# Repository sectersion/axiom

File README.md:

# axiom

modules are 10x15mm note

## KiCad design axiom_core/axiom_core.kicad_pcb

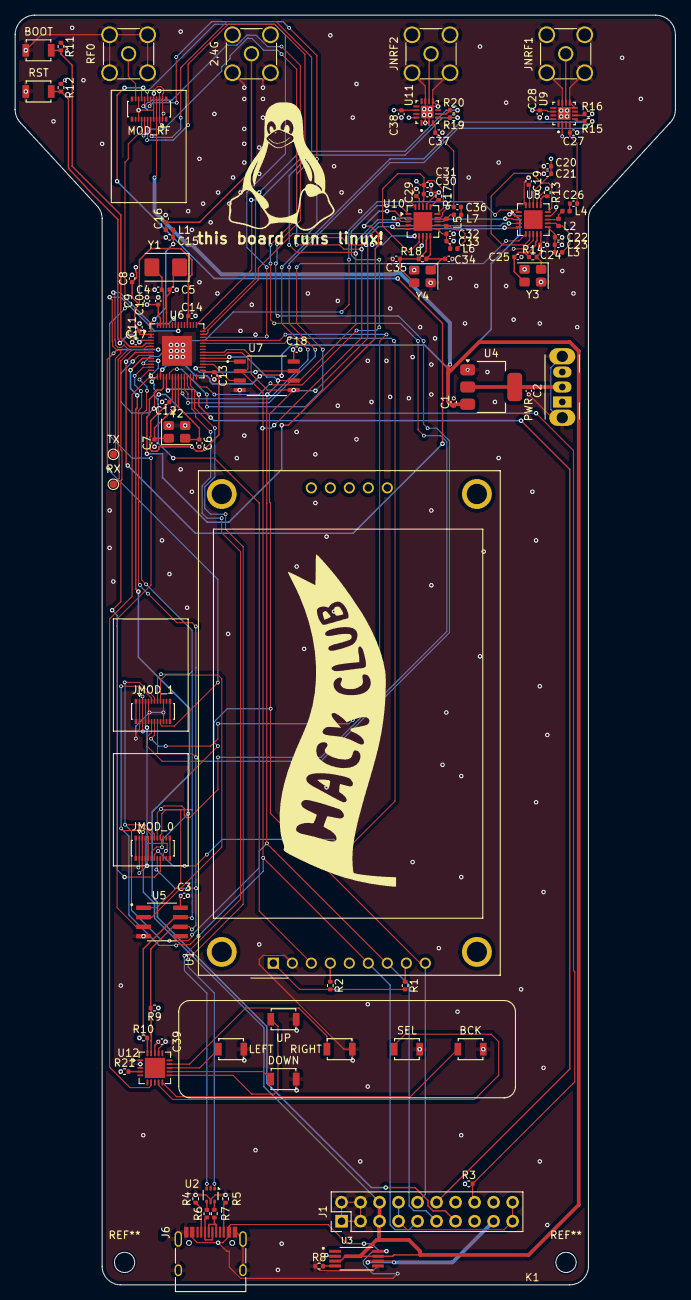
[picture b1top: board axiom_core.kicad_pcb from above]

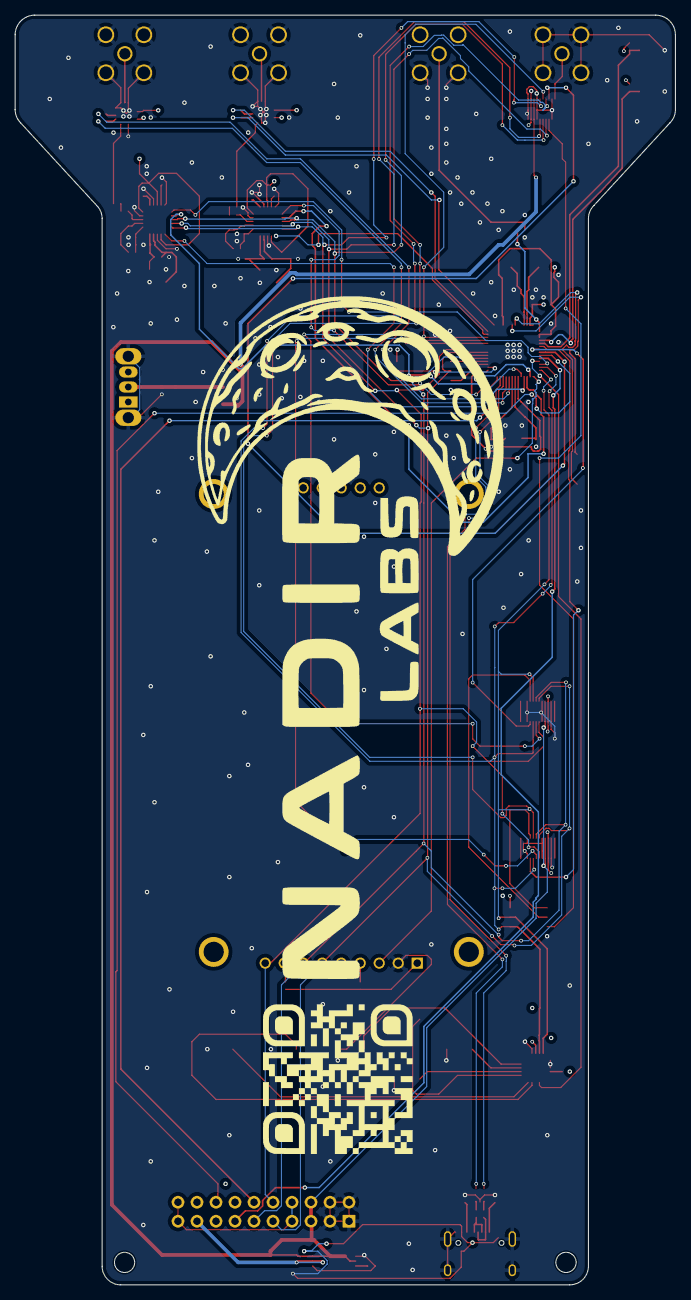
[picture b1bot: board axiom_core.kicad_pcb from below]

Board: 4 copper layers, 88.2 x 169.7 mm, 108 parts (2 on the bottom side), 91 nets.

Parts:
2.4G: ESP32_2.4G; SMA_Amphenol_901-144_Vertical
BCK: BCK; SW_SPST_B3U-1000P
BOOT: BOOT; SW_SPST_B3U-1000P
C1, C10: 10uF; C_0402_1005Metric
C2: 22uF; C_0402_1005Metric
C3, C9, C11, C12, C13, C14, C17, C18, C28, C38, C39: 100nF; C_0402_1005Metric
C4, C5: 18pF; C_0402_1005Metric
C6, C7: 10pF; C_0402_1005Metric
C8: 4.7uF; C_0402_1005Metric
C15, C16: 0pF; C_0402_1005Metric
C19, C29: 33nF; C_0402_1005Metric
C20, C30: 1nF; C_0402_1005Metric
C21, C31: 10nF; C_0402_1005Metric
C22, C26, C32, C36: 4.7pF; C_0402_1005Metric
C23, C33: 2.2nF; C_0402_1005Metric
C24, C25, C34, C35: 12pF; C_0402_1005Metric
C27, C37: 1pF; C_0402_1005Metric
DOWN: DOWN; SW_SPST_B3U-1000P
G12312: LOGO; nl2
G12321: LOGO; tux
G12421: LOGO; hc_flag
G21312: LOGO; github
J1: SHIELD; PinHeader_2x10_P2.54mm_Vertical
J6: USB_C_Receptacle_USB2.0_14P; USB_C_Receptacle_HRO_TYPE-C-31-M-12
JMOD_0, JMOD_1: DF40C-20DP-0.4V_51_; Hirose_DF40C-20DP-0.4V_2x10-1MP_P0.4mm
JNRF1: NRF1; SMA_Amphenol_901-144_Vertical
JNRF2: NRF2; SMA_Amphenol_901-144_Vertical
K1: drill_guide
L1: 2nH; L_0402_1005Metric
L2, L5: 8.2nH; L_0402_1005Metric
L3, L6: 2.7nH; L_0402_1005Metric
L4, L7: 3.9nH; L_0402_1005Metric
LEFT: LEFT; SW_SPST_B3U-1000P
MOD_RF: DF40C-20DP-0.4V_51_; Hirose_DF40C-20DP-0.4V_2x10-1MP_P0.4mm
PWR: SW_Slide_SPDT_Angled_CK_OS102011MA1Q
R1: 10; R_0402_1005Metric
R2, R3, R11, R12, R21: 10k; R_0402_1005Metric
R4, R5: 5.1k; R_0402_1005Metric
R6, R7: 27; R_0402_1005Metric
R8: 100k; R_0402_1005Metric
R9, R10: 4.7k; R_0402_1005Metric
R13, R17: 22k; R_0402_1005Metric
R14, R18: 1M; R_0402_1005Metric
R15, R16, R19, R20: 1k; R_0402_1005Metric
RF0: RF1; SMA_Amphenol_901-144_Vertical
RIGHT: RIGHT; SW_SPST_B3U-1000P
RST: RST; SW_SPST_B3U-1000P
RX: RX; TestPoint_Pad_D1.0mm
SEL: SEL; SW_SPST_B3U-1000P
TX: TX; TestPoint_Pad_D1.0mm
U1: CR2013-MI2120
U2: USBLC6-2P6; SOT-666
U3: TPS2113APW; SOP65P640X120-8N
U4: AMS1117-3.3; SOT-223-3_TabPin2
U5: PCA9536D; SOIC127P599X175-8N
U6: ESP32-S3; QFN-56-1EP_7x7mm_P0.4mm_EP4x4mm
U7: W25Q128JVSIQ; SOIC127P790X216-8N
U8, U10: nRF24L01P; QFN-20-1EP_4x4mm_P0.5mm_EP2.5x2.5mm
U9, U11: RFX2401C
U12: MCP23008-xML; QFN-20-1EP_4x4mm_P0.5mm_EP2.7x2.7mm
UP: UP; SW_SPST_B3U-1000P
Y1: TROQ RG40000421; Crystal_SMD_5032-2Pin_5.0x3.2mm
Y2: EPSON Q13FC13500004; Crystal_SMD_3225-4Pin_3.2x2.5mm
Y3, Y4: XL7EL89COI-111YLC-16M; Crystal_SMD_3225-4Pin_3.2x2.5mm

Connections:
+3V3: C3.1, C8.1, C9.1, C10.1, C11.1, C12.1, C13.1, C14.1, C18.1, C20.2, C21.2, C28.1, C30.2, C31.2, C38.1, C39.2, J1.7, J1.8, J1.19, J1.20, JMOD_0.3, JMOD_0.4, JMOD_1.3, JMOD_1.4, MOD_RF.3, MOD_RF.4, PWR.1, R1.2, R2.2, R3.1, R9.1, R10.1, R11.1, R12.1, R21.1, U1.1 (VCC), U5.8 (VCC), U6.2 (VDD3P3), U6.3 (VDD3P3), U6.20 (VDD3P3_RTC), U6.29 (VDD_SPI), U6.46 (VDD3P3_CPU), U6.55 (VDDA), U6.56 (VDDA), U7.8 (VCC), U8.7 (VDD), U8.15 (VDD), U8.18 (VDD), U9.14 (VDD), U9.16 (VDD), U10.7 (VDD), U10.15 (VDD), U10.18 (VDD), U11.14 (VDD), U11.16 (VDD), U12.18 (VDD)
+5V: C1.1, J1.5, J1.6, JMOD_0.5, JMOD_0.6, JMOD_1.5, JMOD_1.6, MOD_RF.5, MOD_RF.6, U3.3 (VSNS), U3.7 (OUT), U4.3 (VI)
/BTN_IRQ: U6.11 (GPIO6), U12.7 (INT)
/COPROC_CS: J1.12, U6.18 (GPIO13)
/COPROC_IRQ: J1.13, U6.10 (GPIO5)
/GPIO0: JMOD_0.16, U6.6 (GPIO1)
/GPIO1: JMOD_1.16, U6.7 (GPIO2)
/GPIO2: MOD_RF.16, U6.8 (GPIO3)
/IRQ0: JMOD_0.15, U5.1 (P0)
/IRQ1: JMOD_1.15, U5.2 (P1)
/IRQ2: MOD_RF.15, U5.3 (P2)
/MAIN_MISO: J1.10, JMOD_0.10, JMOD_1.10, MOD_RF.10, U1.9 (MISO), U6.35 (SPID), U7.5 (DI(IO0)), U8.5 (MISO), U10.5 (MISO)
/MAIN_MOSI: J1.9, JMOD_0.9, JMOD_1.9, MOD_RF.9, U1.6 (MOSI), U6.34 (SPIQ), U7.2 (DO(IO1)), U8.4 (MOSI), U10.4 (MOSI)
/MAIN_SCL: JMOD_0.14, JMOD_1.14, MOD_RF.14, R9.2, U5.6 (SCL), U6.13 (GPIO8), U12.19 (SCL)
/MAIN_SCLK: J1.11, JMOD_0.11, JMOD_1.11, MOD_RF.11, U1.7 (SCK), U6.33 (SPICLK), U7.6 (CLK), U8.3 (SCK), U10.3 (SCK)
/MAIN_SDA: JMOD_0.13, JMOD_1.13, MOD_RF.13, R10.2, U5.7 (SDA), U6.14 (GPIO9), U12.20 (SDA)
/MCU/ESP32_2.4G: 2.4G.1 (In), C16.2, L1.2
/MCU/LCD_CS: U1.3 (~CS), U6.15 (GPIO10)
/MCU_DM: U2.3 (I/O2), U6.25 (GPIO19/USB_D-)
/MCU_DP: U2.1 (I/O1), U6.26 (GPIO20/USB_D+)
/MOD0_CS: JMOD_0.12, U6.38 (GPIO33)
/MOD1_CS: JMOD_1.12, U6.39 (GPIO34)
/MOD2_CS: MOD_RF.12, U6.40 (GPIO35)
/NRF1_CE: U6.12 (GPIO7), U8.1 (CE)
/NRF1_CS: U6.16 (GPIO11), U8.2 (CSN)
/NRF1_IRQ: U6.19 (GPIO14), U8.6 (IRQ)
/NRF1_RXEN: R16.1, U6.23 (GPIO17)
/NRF1_TXEN: R15.2, U6.24 (GPIO18)
/NRF2_CE: U6.27 (GPIO21), U10.1 (CE)
/NRF2_CS: U6.17 (GPIO12), U10.2 (CSN)
/NRF2_IRQ: U6.41 (GPIO36), U10.6 (IRQ)
/NRF2_RXEN: R20.1, U6.42 (GPIO37)
/NRF2_TXEN: R19.2, U6.43 (GPIO38)
/SHIELD_5V: J1.17, U3.6 (IN2)
/SHIELD_DETECT: J1.16, R3.2, U6.9 (GPIO4)
/button_manager/BCK: BCK.1, U12.10 (GP1)
/button_manager/DOWN: DOWN.1, U12.12 (GP3)
/button_manager/LEFT: LEFT.1, U12.13 (GP4)
/button_manager/RIGHT: RIGHT.1, U12.14 (GP5)
/button_manager/SEL: SEL.1, U12.9 (GP0)
/button_manager/UP: U12.11 (GP2), UP.1
/module_2_rf/ANT: MOD_RF.20, RF0.1 (In)
/nrf_1/NRF_AOUT: JNRF1.1 (In), U9.10 (ANT)
/nrf_2/NRF_AOUT: JNRF2.1 (In), U11.10 (ANT)
GND: 2.4G.2 (Ext), BCK.2, BOOT.1, C1.2, C2.2, C3.2, C4.1, C5.2, C6.2, C7.2, C8.2, C9.2, C10.2, C11.2, C12.2, C13.2, C14.2, C15.2, C16.1, C17.2, C18.2, C19.1, C20.1, C21.1, C22.2, C23.2, C24.2, C25.2, C27.1, C28.2, C29.1, C30.1, C31.1, C32.2, C33.2, C34.2, C35.2, C37.1, C38.2, C39.1, DOWN.2, J1.1, J1.2, J1.3, J1.4, J6.A1 (GND), J6.A12 (GND), J6.B1 (GND), J6.B12 (GND), J6.S1 (SHIELD), JMOD_0.1, JMOD_0.2, JMOD_0.7, JMOD_0.8, JMOD_0.17, JMOD_0.18, JMOD_1.1, JMOD_1.2, JMOD_1.7, JMOD_1.8, JMOD_1.17, JMOD_1.18, JNRF1.2 (Ext), JNRF2.2 (Ext), LEFT.2, MOD_RF.1, MOD_RF.2, MOD_RF.7, MOD_RF.8, MOD_RF.17, MOD_RF.18, R4.2, R5.2, R8.1, R13.1, R17.1, RF0.2 (Ext), RIGHT.2, RST.1, SEL.2, U1.2 (GND), U2.5 (VBUS), U3.2 (~EN), U3.5 (GND), U4.1 (GND), U5.4 (GND), U6.57 (GND), U7.4 (GND), U8.8 (VSS), U8.14 (VSS), U8.17 (VSS), U8.20 (VSS), U9.2 (GND), U9.3 (GND), U9.8 (GND), U9.9 (GND), U9.11 (GND), U9.17 (GND), U10.8 (VSS), U10.14 (VSS), U10.17 (VSS), U10.20 (VSS), U11.2 (GND), U11.3 (GND), U11.8 (GND), U11.9 (GND), U11.11 (GND), U11.17 (GND), U12.1 (A2), U12.2 (A1), U12.3 (A0), U12.17 (VSS), UP.2, Y2.3, Y2.4, Y3.2 (G), Y3.4 (G), Y4.2 (G), Y4.4 (G)
unnamed: C26.1, L4.2
unnamed: C36.1, L7.2
unnamed: J6.A5 (CC1), R4.1
unnamed: J6.B5 (CC2), R5.1
unnamed: J6.A6 (D+), J6.B6 (D+), R7.2
unnamed: J6.A7 (D-), J6.B7 (D-), R6.1
unnamed: R6.2, U2.4 (I/O2)
unnamed: R7.1, U2.6 (I/O1)
unnamed: C2.1, PWR.2, U4.2 (VO)
unnamed: R1.1, U1.8 (LED)
unnamed: R2.1, U1.4 (RESET)
unnamed: R8.2, U3.4 (ILIM)
unnamed: J6.A4 (VBUS), J6.A9 (VBUS), J6.B4 (VBUS), J6.B9 (VBUS), U3.8 (IN1)
unnamed: C17.1, R12.2, RST.2, U6.4 (CHIP_PU)
unnamed: BOOT.2, R11.2, U6.5 (GPIO0)
unnamed: C15.1, L1.1, U6.1 (LNA_IN)
unnamed: U6.32 (SPICS0), U7.1 (/CS)
unnamed: U6.30 (SPIHD), U7.7 (/HOLD/RESET(IO3))
unnamed: U6.31 (SPIWP), U7.3 (/WP(IO2))
unnamed: RX.1, U6.50 (U0RXD)
unnamed: TX.1, U6.49 (U0TXD)
unnamed: C6.1, U6.22 (XTAL_32K_N), Y2.2
unnamed: C7.1, U6.21 (XTAL_32K_P), Y2.1
unnamed: C5.1, U6.53 (XTAL_N), Y1.1
unnamed: C4.2, U6.54 (XTAL_P), Y1.2
unnamed: L2.1, L3.2, U8.12 (ANT1)
unnamed: L2.2, L4.1, U8.13 (ANT2)
unnamed: C19.2, U8.19 (DVDD)
unnamed: R13.2, U8.16 (IREF)
unnamed: C22.1, C23.1, L3.1, U8.11 (VDD_PA)
unnamed: C24.1, R14.1, U8.10 (XC1), Y3.1
unnamed: C25.1, R14.2, U8.9 (XC2), Y3.3
unnamed: R16.2, U9.6 (RXEN)
unnamed: R15.1, U9.5 (TXEN)
unnamed: C26.2, C27.2, U9.4 (TXRX)
unnamed: L5.1, L6.2, U10.12 (ANT1)
unnamed: L5.2, L7.1, U10.13 (ANT2)
unnamed: C29.2, U10.19 (DVDD)
unnamed: R17.2, U10.16 (IREF)
unnamed: C32.1, C33.1, L6.1, U10.11 (VDD_PA)
unnamed: C34.1, R18.1, U10.10 (XC1), Y4.1
unnamed: C35.1, R18.2, U10.9 (XC2), Y4.3
unnamed: R20.2, U11.6 (RXEN)
unnamed: R19.1, U11.5 (TXEN)
unnamed: C36.2, C37.2, U11.4 (TXRX)
unnamed: R21.2, U12.4 (~RESET)

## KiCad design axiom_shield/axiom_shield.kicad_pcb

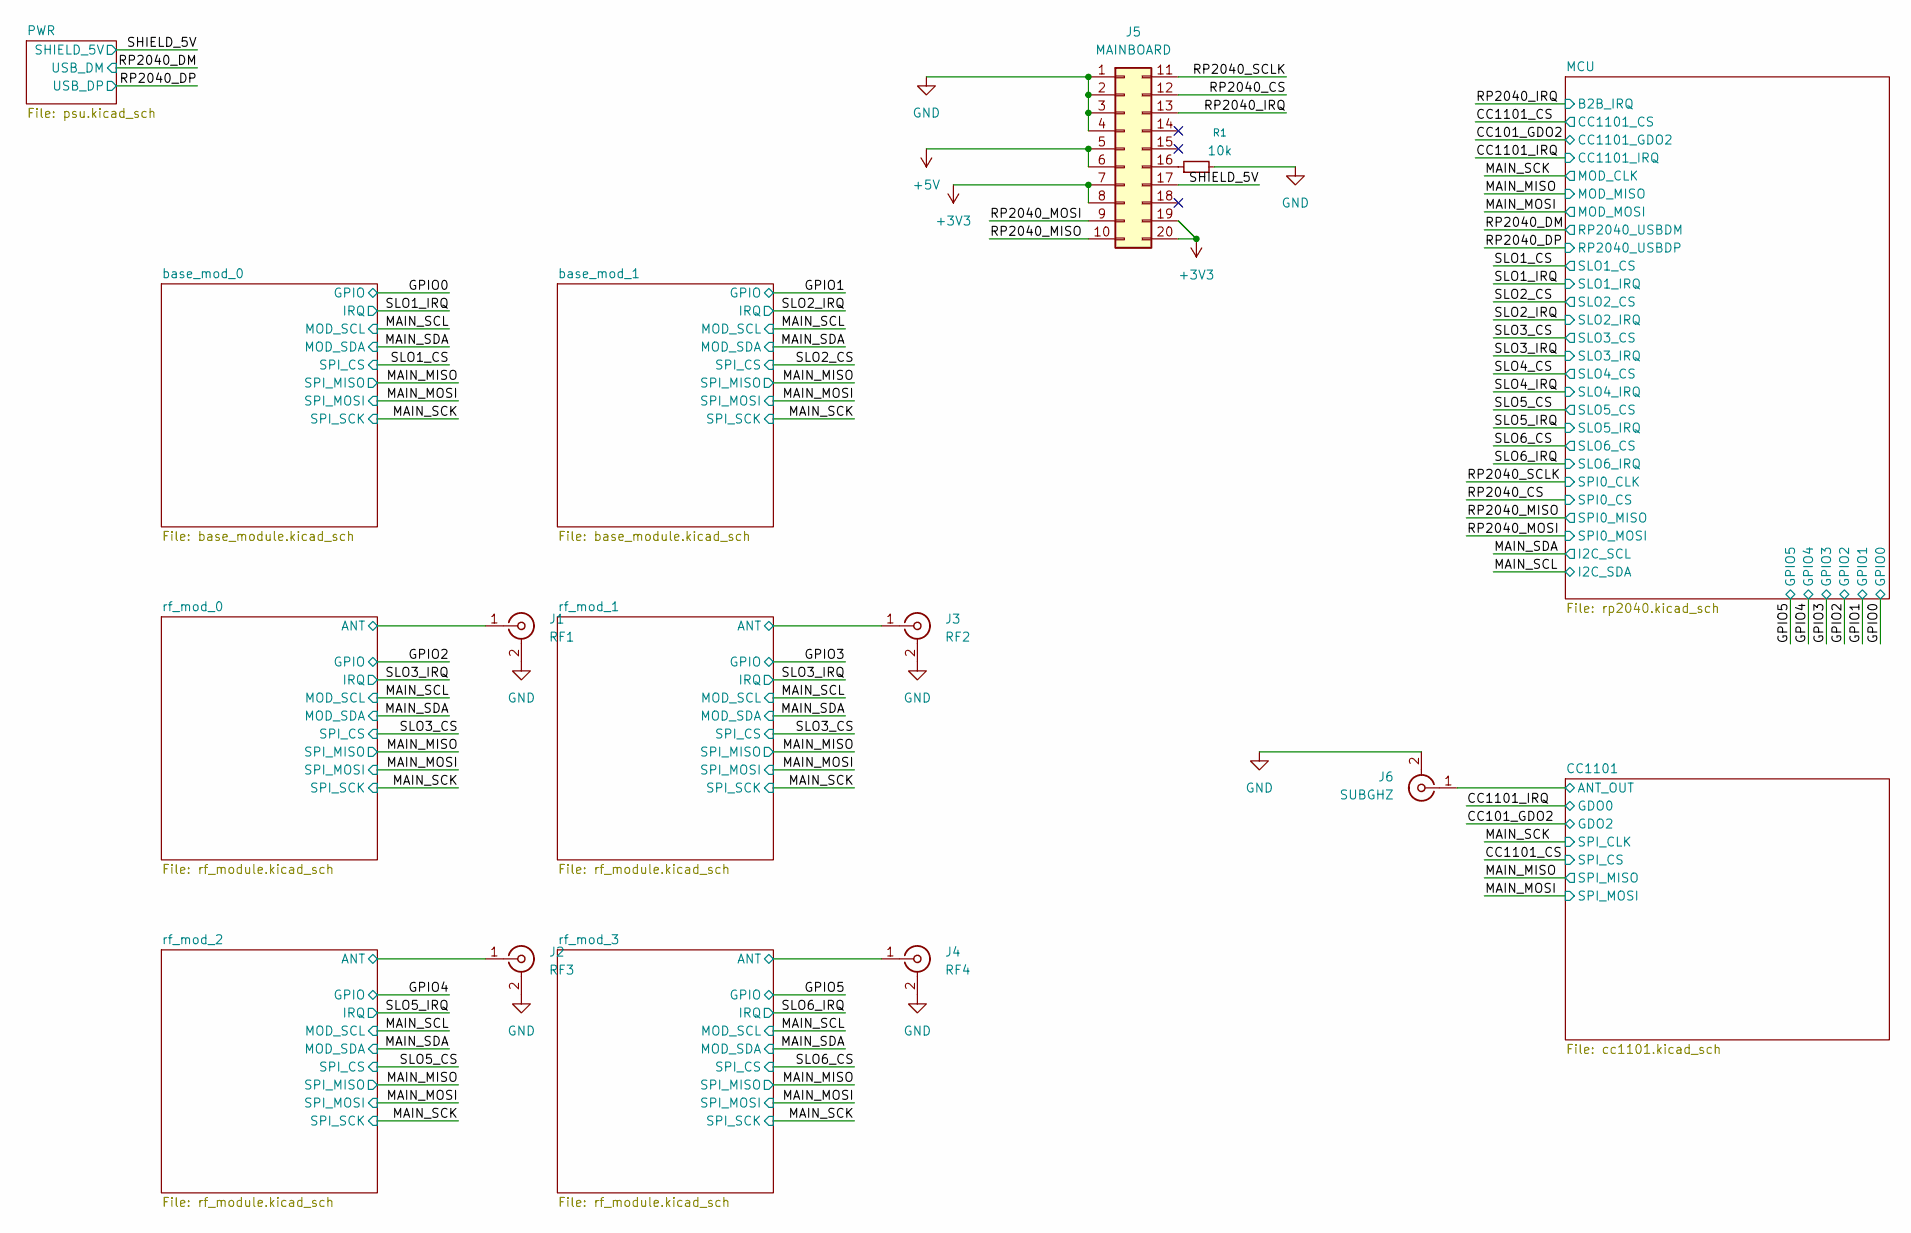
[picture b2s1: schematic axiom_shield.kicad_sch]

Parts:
J1: RF1; SMA_Amphenol_901-144_Vertical
J2: RF3; SMA_Amphenol_901-144_Vertical
J3: RF2; SMA_Amphenol_901-144_Vertical
J4: RF4; SMA_Amphenol_901-144_Vertical
J5: MAINBOARD; PinSocket_2x10_P2.54mm_Vertical
J6: SUBGHZ; SMA_Amphenol_901-144_Vertical
R1: 10k; R_0402_1005Metric

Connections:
/CC1101/ANT_OUT: J6.1 (In); also elsewhere on the board
/rf_mod_0/ANT: J1.1 (In); also elsewhere on the board
/rf_mod_1/ANT: J3.1 (In); also elsewhere on the board
/rf_mod_2/ANT: J2.1 (In); also elsewhere on the board
/rf_mod_3/ANT: J4.1 (In); also elsewhere on the board
GND: J1.2 (Ext), J2.2 (Ext), J3.2 (Ext), J4.2 (Ext), J5.1, J5.2, J5.3, J5.4, J6.2 (Ext), R1.2; also elsewhere on the board
unnamed: J5.5, J5.6
unnamed: J5.7, J5.8, J5.19, J5.20
unnamed 47: J5.16, R1.1; also elsewhere on the board

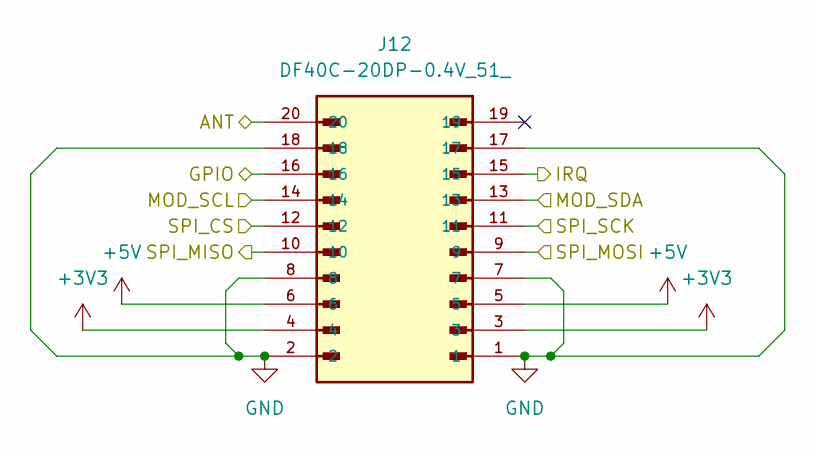
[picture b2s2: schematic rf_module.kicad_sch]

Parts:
J12: DF40C-20DP-0.4V_51_; HRS_DF40C-20DP-0.4V_51_; PARTREV 02/2020

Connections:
+3V3: J12.3, J12.4; also elsewhere on the board
+5V: J12.5, J12.6; also elsewhere on the board
/GPIO2: J12.16; also elsewhere on the board
/MAIN_MISO: J12.10; also elsewhere on the board
/MAIN_MOSI: J12.9; also elsewhere on the board
/MAIN_SCK: J12.11; also elsewhere on the board
/MAIN_SCL: J12.14; also elsewhere on the board
/MAIN_SDA: J12.13; also elsewhere on the board
/SLO3_CS: J12.12; also elsewhere on the board
/SLO3_IRQ: J12.15; also elsewhere on the board
/rf_mod_0/ANT: J12.20; also elsewhere on the board
GND: J12.1, J12.2, J12.7, J12.8, J12.17, J12.18; also elsewhere on the board

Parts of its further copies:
J13, J14, J15: DF40C-20DP-0.4V_51_; HRS_DF40C-20DP-0.4V_51_; PARTREV 02/2020

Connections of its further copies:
+3V3: J13.3, J13.4, J14.3, J14.4, J15.3, J15.4; also elsewhere on the board
+5V: J13.5, J13.6, J14.5, J14.6, J15.5, J15.6; also elsewhere on the board
/GPIO3: J13.16; also elsewhere on the board
/GPIO4: J14.16; also elsewhere on the board
/GPIO5: J15.16; also elsewhere on the board
/MAIN_MISO: J13.10, J14.10, J15.10; also elsewhere on the board
/MAIN_MOSI: J13.9, J14.9, J15.9; also elsewhere on the board
/MAIN_SCK: J13.11, J14.11, J15.11; also elsewhere on the board
/MAIN_SCL: J13.14, J14.14, J15.14; also elsewhere on the board
/MAIN_SDA: J13.13, J14.13, J15.13; also elsewhere on the board
/SLO3_CS: J13.12; also elsewhere on the board
/SLO3_IRQ: J13.15; also elsewhere on the board
/SLO5_CS: J14.12; also elsewhere on the board
/SLO5_IRQ: J14.15; also elsewhere on the board
/SLO6_CS: J15.12; also elsewhere on the board
/SLO6_IRQ: J15.15; also elsewhere on the board
/rf_mod_1/ANT: J13.20; also elsewhere on the board
/rf_mod_2/ANT: J14.20; also elsewhere on the board
/rf_mod_3/ANT: J15.20; also elsewhere on the board
GND: J13.1, J13.2, J13.7, J13.8, J13.17, J13.18, J14.1, J14.2, J14.7, J14.8, J14.17, J14.18, J15.1, J15.2, J15.7, J15.8, J15.17, J15.18; also elsewhere on the board

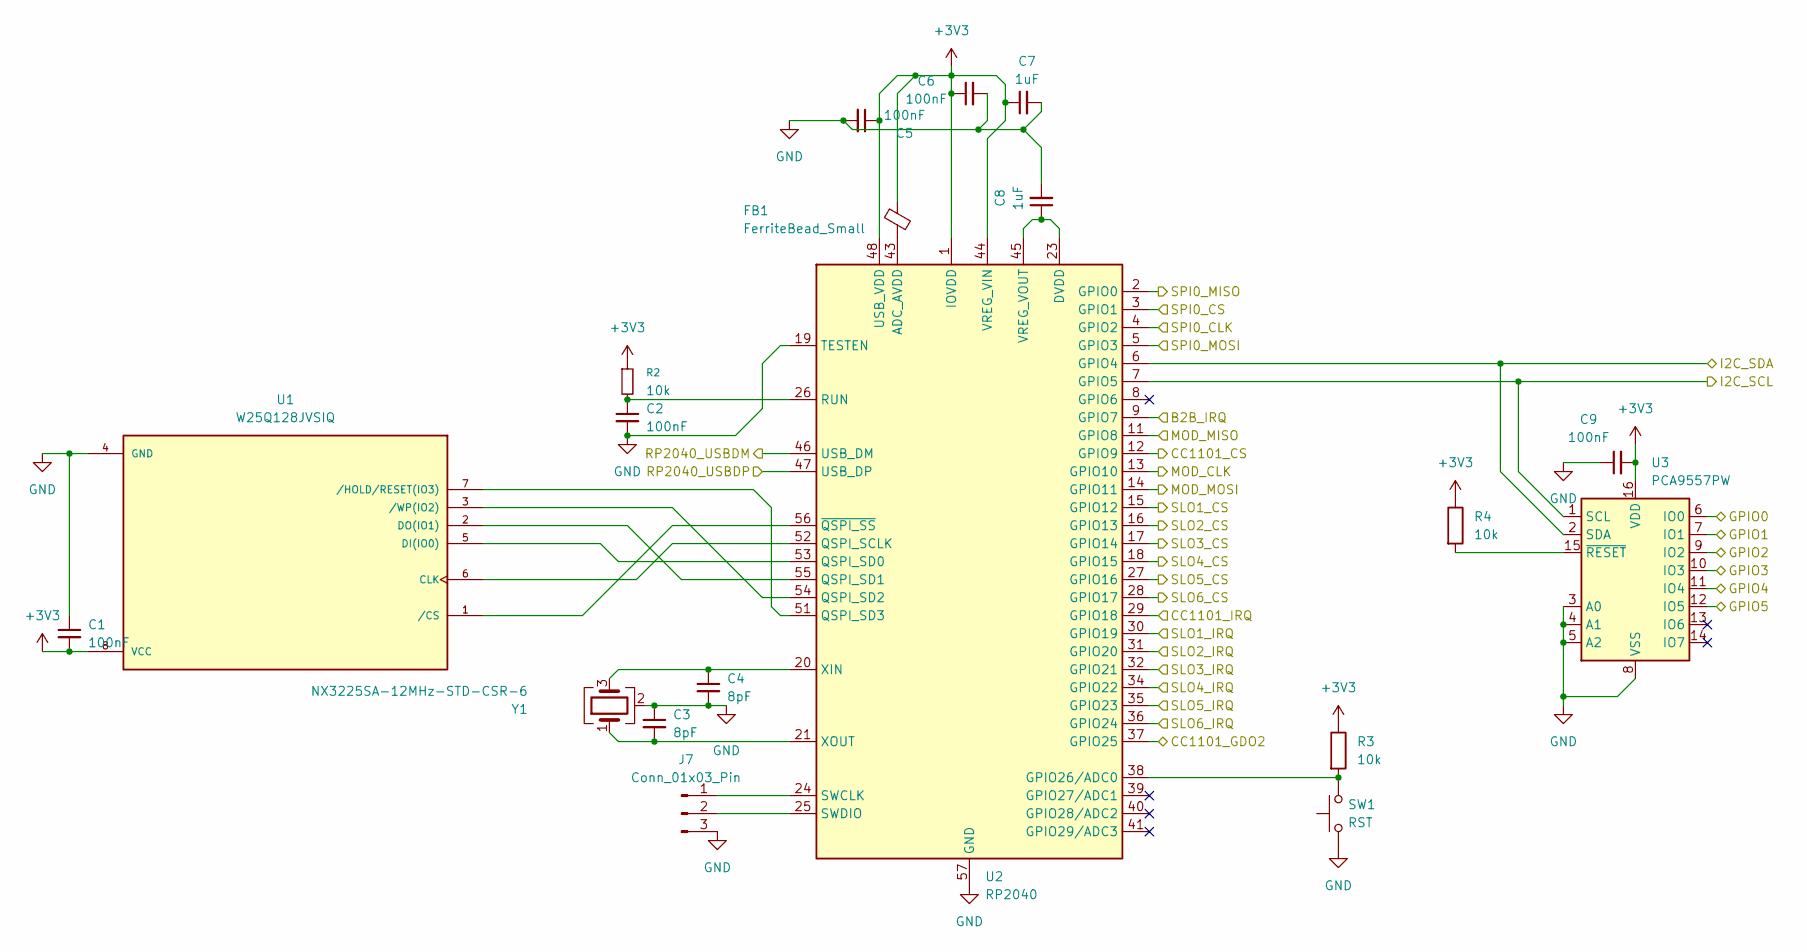
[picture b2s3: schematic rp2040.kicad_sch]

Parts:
C1, C2, C5, C6, C9: 100nF; C_0402_1005Metric
C3, C4: 8pF; C_0402_1005Metric
C7, C8: 1uF; C_0402_1005Metric
FB1: FerriteBead_Small; L_0402_1005Metric
J7: Conn_01x03_Pin; PinHeader_1x03_P2.54mm_Vertical
R2, R3, R4: 10k; R_0402_1005Metric
SW1: RST; SW_SPST_B3U-1000P
U1: W25Q128JVSIQ; SOIC127P790X216-8N; PARTREV I
U2: RP2040; QFN-56-1EP_7x7mm_P0.4mm_EP3.2x3.2mm
U3: PCA9557PW; TSSOP-16_4.4x5mm_P0.65mm
Y1: NX3225SA-12MHz-STD-CSR-6; Crystal_SMD_3225-4Pin_3.2x2.5mm

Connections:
+3V3: C1.2, C5.1, C6.1, C7.1, C9.2, FB1.1, R2.1, R3.1, R4.1, U1.8 (VCC), U2.1 (IOVDD), U2.10 (IOVDD), U2.22 (IOVDD), U2.33 (IOVDD), U2.42 (IOVDD), U2.44 (VREG_VIN), U2.48 (USB_VDD), U2.49 (IOVDD), U3.16 (VDD); also elsewhere on the board
/CC101_GDO2: U2.37 (GPIO25); also elsewhere on the board
/CC1101_CS: U2.12 (GPIO9); also elsewhere on the board
/CC1101_IRQ: U2.29 (GPIO18); also elsewhere on the board
/GPIO0: U3.6 (IO0); also elsewhere on the board
/GPIO1: U3.7 (IO1); also elsewhere on the board
/GPIO2: U3.9 (IO2); also elsewhere on the board
/GPIO3: U3.10 (IO3); also elsewhere on the board
/GPIO4: U3.11 (IO4); also elsewhere on the board
/GPIO5: U3.12 (IO5); also elsewhere on the board
/MAIN_MISO: U2.11 (GPIO8); also elsewhere on the board
/MAIN_MOSI: U2.14 (GPIO11); also elsewhere on the board
/MAIN_SCK: U2.13 (GPIO10); also elsewhere on the board
/MAIN_SCL: U2.6 (GPIO4), U3.2 (SDA); also elsewhere on the board
/MAIN_SDA: U2.7 (GPIO5), U3.1 (SCL); also elsewhere on the board
/RP2040_CS: U2.3 (GPIO1); also elsewhere on the board
/RP2040_DM: U2.46 (USB_DM); also elsewhere on the board
/RP2040_DP: U2.47 (USB_DP); also elsewhere on the board
/RP2040_IRQ: U2.9 (GPIO7); also elsewhere on the board
/RP2040_MISO: U2.2 (GPIO0); also elsewhere on the board
/RP2040_MOSI: U2.5 (GPIO3); also elsewhere on the board
/RP2040_SCLK: U2.4 (GPIO2); also elsewhere on the board
/SLO1_CS: U2.15 (GPIO12); also elsewhere on the board
/SLO1_IRQ: U2.30 (GPIO19); also elsewhere on the board
/SLO2_CS: U2.16 (GPIO13); also elsewhere on the board
/SLO2_IRQ: U2.31 (GPIO20); also elsewhere on the board
/SLO3_CS: U2.17 (GPIO14); also elsewhere on the board
/SLO3_IRQ: U2.32 (GPIO21); also elsewhere on the board
/SLO4_CS: U2.18 (GPIO15)
/SLO4_IRQ: U2.34 (GPIO22)
/SLO5_CS: U2.27 (GPIO16); also elsewhere on the board
/SLO5_IRQ: U2.35 (GPIO23); also elsewhere on the board
/SLO6_CS: U2.28 (GPIO17); also elsewhere on the board
/SLO6_IRQ: U2.36 (GPIO24); also elsewhere on the board
GND: C1.1, C2.2, C3.1, C4.2, C5.2, C6.2, C7.2, C8.2, C9.1, J7.3, SW1.1, U1.4 (GND), U2.19 (TESTEN), U2.57 (GND), U3.3 (A0), U3.4 (A1), U3.5 (A2), U3.8 (VSS), Y1.2 (G), Y1.4 (G); also elsewhere on the board
unnamed: J7.1, U2.24 (SWCLK)
unnamed: J7.2, U2.25 (SWDIO)
unnamed: U1.6 (CLK), U2.52 (QSPI_SCLK)
unnamed: U1.5 (DI(IO0)), U2.53 (QSPI_SD0)
unnamed: U1.2 (DO(IO1)), U2.55 (QSPI_SD1)
unnamed: U1.1 (/CS), U2.56 (~QSPI_SS)
unnamed: U1.7 (/HOLD/RESET(IO3)), U2.51 (QSPI_SD3)
unnamed: U1.3 (/WP(IO2)), U2.54 (QSPI_SD2)
unnamed: FB1.2, U2.43 (ADC_AVDD)
unnamed: R3.2, SW1.2, U2.38 (GPIO26/ADC0)
unnamed: C2.1, R2.2, U2.26 (RUN)
unnamed: C8.1, U2.23 (DVDD), U2.45 (VREG_VOUT), U2.50 (DVDD)
unnamed: C4.1, U2.20 (XIN), Y1.3
unnamed: C3.2, U2.21 (XOUT), Y1.1
unnamed: R4.2, U3.15 (~RESET)

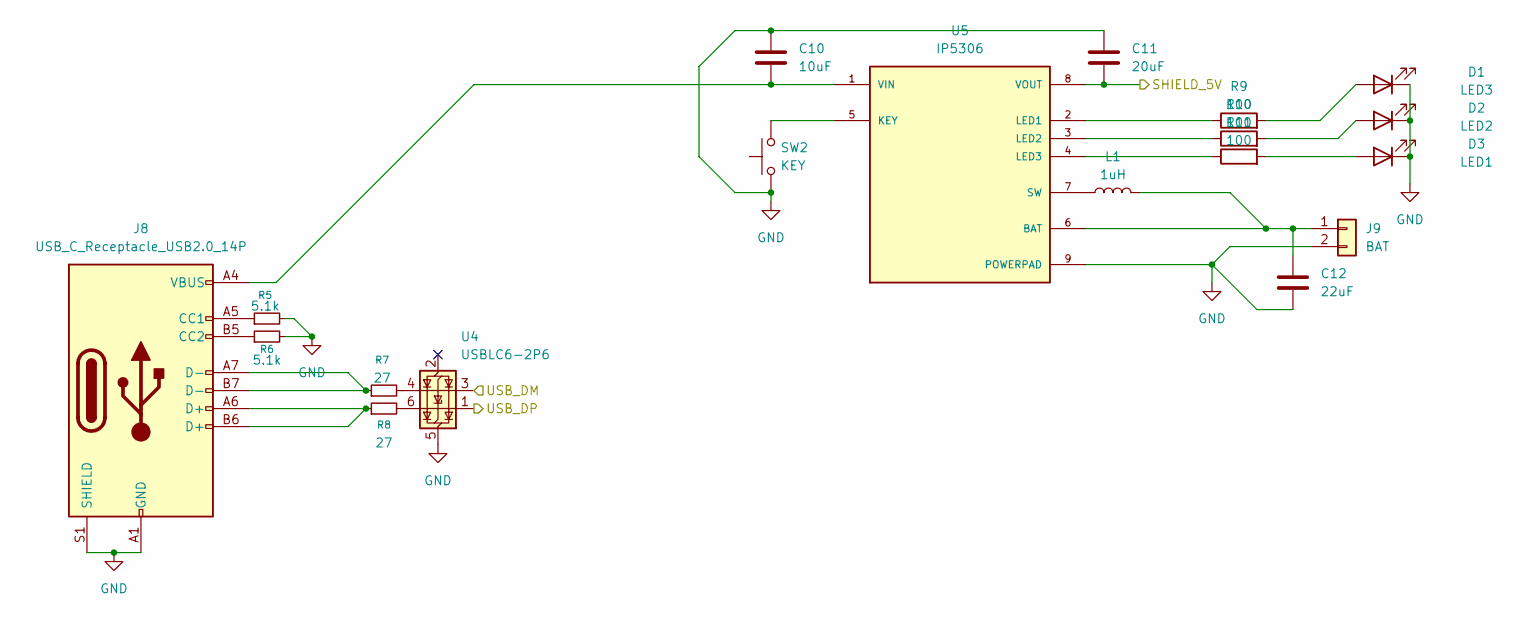
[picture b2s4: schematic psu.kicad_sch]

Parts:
C10: 10uF; C_0402_1005Metric
C11: 20uF; C_0402_1005Metric
C12: 22uF; C_0402_1005Metric
D1: LED3; LED_0603_1608Metric
D2: LED2; LED_0603_1608Metric
D3: LED1; LED_0603_1608Metric
J8: USB_C_Receptacle_USB2.0_14P; USB_C_Receptacle_HRO_TYPE-C-31-M-12
J9: BAT; JST_PH_B2B-PH-K_1x02_P2.00mm_Vertical
L1: 1uH; L_0402_1005Metric
R5, R6: 5.1k; R_0402_1005Metric
R7, R8: 27; R_0402_1005Metric
R9, R10, R11: 100; R_0402_1005Metric
SW2: KEY; SW_SPST_B3U-1000P
U4: USBLC6-2P6; SOT-666
U5: IP5306; ip5306; PARTREV 1.31

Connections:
/RP2040_DM: U4.3 (I/O2); also elsewhere on the board
/RP2040_DP: U4.1 (I/O1); also elsewhere on the board
/SHIELD_5V: C11.2, U5.8 (VOUT); also elsewhere on the board
GND: C10.1, C11.1, C12.2, D1.1 (K), D2.1 (K), D3.1 (K), J8.A1 (GND), J8.A12 (GND), J8.B1 (GND), J8.B12 (GND), J8.S1 (SHIELD), J9.2, R5.2, R6.2, SW2.1, U4.5 (VBUS), U5.9 (POWERPAD); also elsewhere on the board
unnamed: D1.2 (A), R9.2
unnamed: D2.2 (A), R10.2
unnamed: D3.2 (A), R11.2
unnamed: J8.A5 (CC1), R5.1
unnamed: J8.B5 (CC2), R6.1
unnamed: J8.A6 (D+), J8.B6 (D+), R8.1
unnamed: J8.A7 (D-), J8.B7 (D-), R7.1
unnamed: C12.1, J9.1, L1.2, U5.6 (BAT)
unnamed: R7.2, U4.4 (I/O2)
unnamed: R8.2, U4.6 (I/O1)
unnamed: SW2.2, U5.5 (KEY)
unnamed: R9.1, U5.2 (LED1)
unnamed: R10.1, U5.3 (LED2)
unnamed: R11.1, U5.4 (LED3)
unnamed: L1.1, U5.7 (SW)
unnamed: C10.2, J8.A4 (VBUS), J8.A9 (VBUS), J8.B4 (VBUS), J8.B9 (VBUS), U5.1 (VIN)

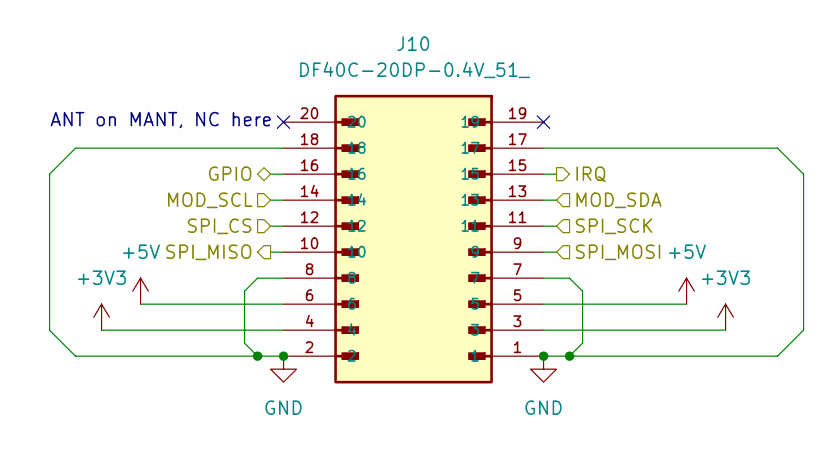
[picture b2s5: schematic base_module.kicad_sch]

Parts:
J10: DF40C-20DP-0.4V_51_; HRS_DF40C-20DP-0.4V_51_; PARTREV 02/2020

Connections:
+3V3: J10.3, J10.4; also elsewhere on the board
+5V: J10.5, J10.6; also elsewhere on the board
/GPIO0: J10.16; also elsewhere on the board
/MAIN_MISO: J10.10; also elsewhere on the board
/MAIN_MOSI: J10.9; also elsewhere on the board
/MAIN_SCK: J10.11; also elsewhere on the board
/MAIN_SCL: J10.14; also elsewhere on the board
/MAIN_SDA: J10.13; also elsewhere on the board
/SLO1_CS: J10.12; also elsewhere on the board
/SLO1_IRQ: J10.15; also elsewhere on the board
GND: J10.1, J10.2, J10.7, J10.8, J10.17, J10.18; also elsewhere on the board

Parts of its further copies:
J11: DF40C-20DP-0.4V_51_; HRS_DF40C-20DP-0.4V_51_; PARTREV 02/2020

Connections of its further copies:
+3V3: J11.3, J11.4; also elsewhere on the board
+5V: J11.5, J11.6; also elsewhere on the board
/GPIO1: J11.16; also elsewhere on the board
/MAIN_MISO: J11.10; also elsewhere on the board
/MAIN_MOSI: J11.9; also elsewhere on the board
/MAIN_SCK: J11.11; also elsewhere on the board
/MAIN_SCL: J11.14; also elsewhere on the board
/MAIN_SDA: J11.13; also elsewhere on the board
/SLO2_CS: J11.12; also elsewhere on the board
/SLO2_IRQ: J11.15; also elsewhere on the board
GND: J11.1, J11.2, J11.7, J11.8, J11.17, J11.18; also elsewhere on the board

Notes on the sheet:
ANT on MANT, NC here

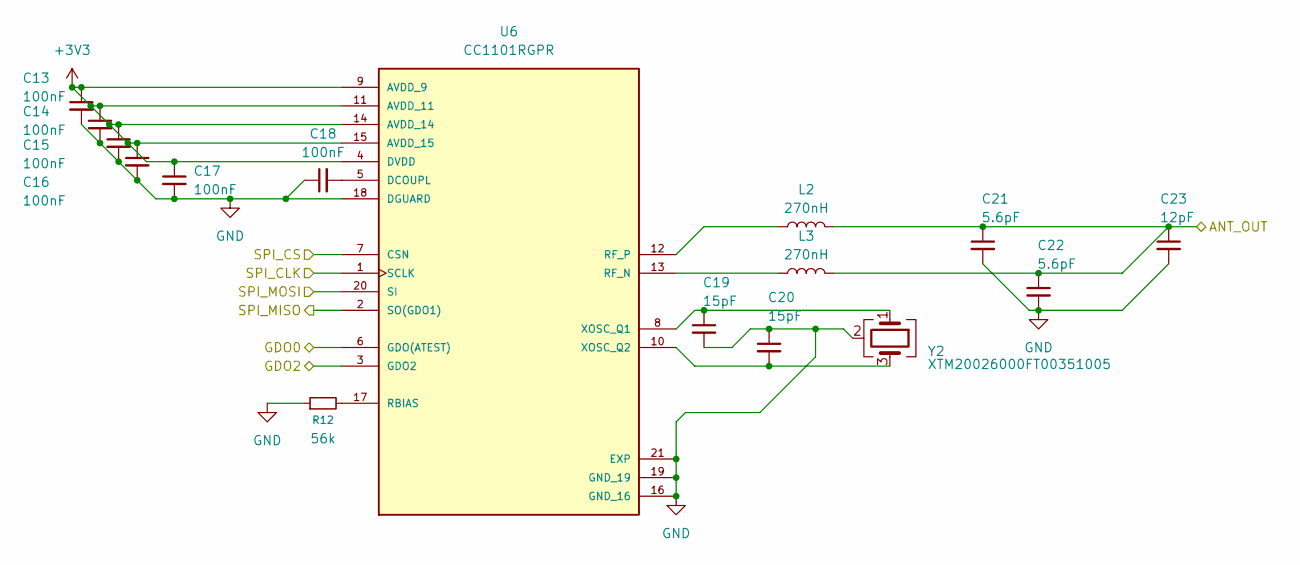
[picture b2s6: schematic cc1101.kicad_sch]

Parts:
C13, C14, C15, C16, C17, C18: 100nF; C_0402_1005Metric
C19, C20: 15pF; C_0402_1005Metric
C21, C22: 5.6pF; C_0402_1005Metric
C23: 12pF; C_0402_1005Metric
L2, L3: 270nH; L_0402_1005Metric
R12: 56k; R_0402_1005Metric
U6: CC1101RGPR; cc1101; PARTREV 6-May-2020
Y2: XTM20026000FT00351005; Crystal_SMD_2016-4Pin_2.0x1.6mm

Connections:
+3V3: C13.1, C14.1, C15.1, C16.1, C17.1, U6.4 (DVDD), U6.9 (AVDD_9), U6.11 (AVDD_11), U6.14 (AVDD_14), U6.15 (AVDD_15); also elsewhere on the board
/CC101_GDO2: U6.3 (GDO2); also elsewhere on the board
/CC1101/ANT_OUT: C21.1, C22.1, C23.1, L2.2, L3.2; also elsewhere on the board
/CC1101_CS: U6.7 (CSN); also elsewhere on the board
/CC1101_IRQ: U6.6 (GDO(ATEST)); also elsewhere on the board
/MAIN_MISO: U6.2 (SO(GDO1)); also elsewhere on the board
/MAIN_MOSI: U6.20 (SI); also elsewhere on the board
/MAIN_SCK: U6.1 (SCLK); also elsewhere on the board
GND: C13.2, C14.2, C15.2, C16.2, C17.2, C18.1, C19.2, C20.1, C21.2, C22.2, C23.2, R12.1, U6.16 (GND_16), U6.18 (DGUARD), U6.19 (GND_19), U6.21 (EXP), Y2.2 (G), Y2.4 (G); also elsewhere on the board
unnamed: C18.2, U6.5 (DCOUPL)
unnamed: R12.2, U6.17 (RBIAS)
unnamed: L3.1, U6.13 (RF_N)
unnamed: L2.1, U6.12 (RF_P)
unnamed: C19.1, U6.8 (XOSC_Q1), Y2.1
unnamed: C20.2, U6.10 (XOSC_Q2), Y2.3

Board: 2 copper layers, 68 parts (0 on the bottom side), 78 nets, no tracks yet.

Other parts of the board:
K2: drill_guide
MAIN: MAINBOARD; PinSocket_2x10_P2.54mm_Vertical

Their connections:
+3V3: MAIN.7, MAIN.8, MAIN.19, MAIN.20; also elsewhere on the board
+5V: MAIN.5, MAIN.6; also elsewhere on the board
/RP2040_CS: MAIN.11; also elsewhere on the board
/RP2040_IRQ: MAIN.14; also elsewhere on the board
/RP2040_MISO: MAIN.9; also elsewhere on the board
/RP2040_MOSI: MAIN.10; also elsewhere on the board
/RP2040_SCLK: MAIN.12; also elsewhere on the board
/SHIELD_5V: MAIN.18; also elsewhere on the board
GND: MAIN.1, MAIN.2, MAIN.3, MAIN.4; also elsewhere on the board
unnamed 47: MAIN.15; also elsewhere on the board

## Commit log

2026-04-07 upload
